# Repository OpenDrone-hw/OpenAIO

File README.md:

# OpenAIO

An all-in-one for 85 mm whoops, 2.5 inch cinewhoops and 3 inch freestyle: RP2354A flight controller, four AM32 ESC channels and an ExpressLRS 2.4 GHz
receiver on one 8-layer HDI board with 25.5 x 25.5 mm mounting. Its circuits follow OpenFC Lite 20x20, OpenESC-20x20 and
OpenRX-Lite.

## Why

Flight controller, ESC and receiver are usually three boards joined by connectors and wiring. On a small quad the
stack costs weight and height, and the connectors are where builds fail. OpenAIO puts all three on one board and keeps
the firmware stock. The market research linked under Prior art covers competing AIOs.

## Specifications

From the design files. Not manufactured yet.

| | |
|---|---|
| Mounting | 25.5 x 25.5 mm, four 3.0 mm holes |
| Board | 35.4 x 35.4 mm, 8 layers HDI 1+6+1, 0.997 mm, 1 oz copper on all layers, ENIG |
| Input | 3S to 6S LiPo, 9.0 to 25.2 V; 2S is not supported (gate driver VCC, see research/INPUT_RANGE.md) |
| Input protection | None: no reverse polarity protection, no TVS. Fit a low-ESR electrolytic of at least 35 V on the battery leads |
| Current rating | Not established; no measurement exists |
| Flight controller | RP2354A, BMI270 IMU, BMP580 barometer, USB-C |
| OSD and blackbox | Analog PIO framebuffer OSD, microSD card |
| ESC | 4x AM32, AT32F421G8U7 + NSG2065Q + 6x DOY180N03T (30 V) per channel, one shared current sensor |
| Receiver | ExpressLRS 2.4 GHz, ESP32-C3 + SX1281, u.FL antenna |
| Outputs | +10V (always on with a battery) on SH-6 and pads, +5V and +4v5 pads, WS2812 strip pads, buzzer pads |
| Firmware | Betaflight, AM32, ExpressLRS, stock upstream |

Technical write-up, part list and layout constraints: [AGENTS.md](AGENTS.md). Pinout and firmware:
[firmware/](firmware/README.md).

## Constraints

- 25.5 x 25.5 mm mounting, the whoop and toothpick standard.
- Runs stock firmware: Betaflight on the FC, AM32 per ESC channel, ExpressLRS on the receiver. No forks.
- Parts come from the shared library first; assembly from LCSC parts, extended parts kept to a minimum.
- 8-layer HDI 1+6+1 with filled microvias; fabrication limits are in [research/NEXTPCB.md](research/NEXTPCB.md).

## Prior art

- [OpenFC Lite 20x20](https://github.com/OpenDrone-hw/OpenFC-Lite-Mini): the RP2354A flight controller
- [OpenESC-20x20](https://github.com/OpenDrone-hw/OpenESC-20x20): the AM32 4-in-1 power stage
- [OpenRX Lite](https://github.com/OpenDrone-hw/OpenRX-Lite): the ELRS receiver
- [Market research](https://app.notion.com/p/3f5fe06764e1818e9158c512edd58138): competing toothpick and whoop AIOs, June 2026
- [Part alternatives](https://app.notion.com/p/3f5fe06764e1819eade0dc5bfbfdff7c): ESC-stage part alternatives, gate driver and FET options, March 2026
- [Current sensing](research/shunt/MARKET_AND_LITERATURE.md): shunt against copper sensing, market and literature

Notes: [input range](research/INPUT_RANGE.md), [pin constraints](research/IO-CONSTRAINTS.md),
[board data and copper model](research/ROUTING.md).

## Design questions

- Thermal: four power stages next to an MCU and a radio on 25.5 mm square, with no airflow guarantee. What is the
  continuous current budget on 1 oz copper? The copper loss model in [research/ROUTING.md](research/ROUTING.md) is the
  only number so far.
- RF isolation: a 2.4 GHz receiver next to four switching power stages: ground plane and antenna placement are
  untested.
- Open board issues: the LED strip stage inverts, the ESC MCUs run from USB without gate drive power, and SBUS on
  SH-6 shares a net with the ELRS TX: [firmware/ISSUES.md](firmware/ISSUES.md).

## In the line

What pairs with what, and what is available:
[opendrone.be](https://opendrone.be).

## Contributing

KiCad files cannot be merged, so say what you intend to change before you do,
on [Discord](https://discord.gg/v3sWmTcx3R). How everything works:
[CONTRIBUTING.md](CONTRIBUTING.md).

A repository holds design files only. Sourcing (suppliers, prices, quotes, RFQs, contacts) is handled by Incutec and never lives in OpenDrone repositories.

## License

Hardware licensed under [CERN-OHL-S-2.0](https://ohwr.org/cern_ohl_s_v2.txt),
see [LICENSE](LICENSE).

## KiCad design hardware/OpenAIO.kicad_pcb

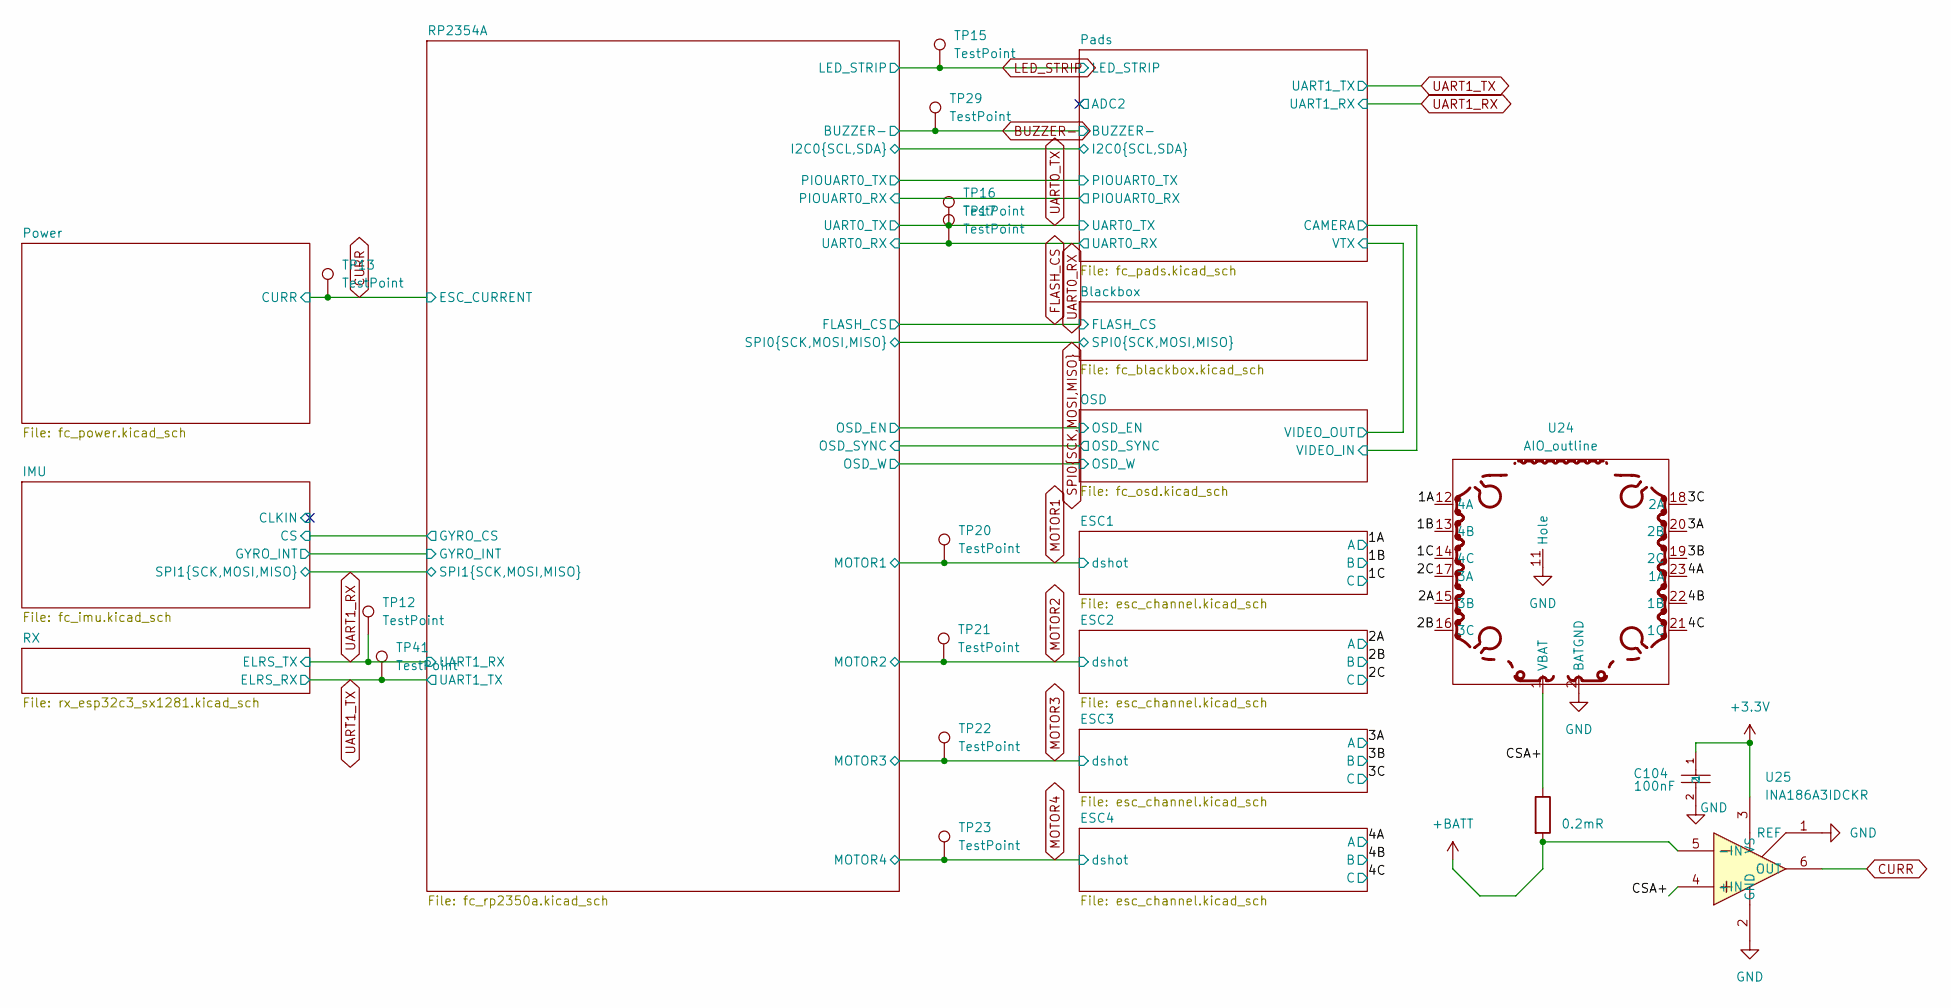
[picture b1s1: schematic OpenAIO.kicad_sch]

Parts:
C104: 100nF; C_0201_0603Metric; MPN GRM033R6YA104KE14D; LCSC C181043
Rsense2: 0.2mR; R_2512_6332Metric; MPN ASR-S-3-0.2F; LCSC C695806
TP12, TP13, TP15, TP16, TP17, TP20, TP21, TP22, TP23, TP29, TP41: TestPoint; TestPoint_Pad_D1.0mm
U24: AIO_outline
U25: INA186A3IDCKR; SOT-363_SC-70-6; MPN INA186A3IDCKR; LCSC C2058245

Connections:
+3.3V: C104.1, U25.3 (VS); also elsewhere on the board
+BATT: Rsense2.2, U25.5 (-IN); also elsewhere on the board
/1A: U24.12 (4A); also elsewhere on the board
/1B: U24.13 (4B); also elsewhere on the board
/1C: U24.14 (4C); also elsewhere on the board
/2A: U24.15 (3B); also elsewhere on the board
/2B: U24.16 (3C); also elsewhere on the board
/2C: U24.17 (3A); also elsewhere on the board
/3A: U24.20 (2B); also elsewhere on the board
/3B: U24.19 (2C); also elsewhere on the board
/3C: U24.18 (2A); also elsewhere on the board
/4A: U24.23 (1A); also elsewhere on the board
/4B: U24.22 (1B); also elsewhere on the board
/4C: U24.21 (1C); also elsewhere on the board
/CSA+: Rsense2.1, U24.1 (VBAT), U25.4 (+IN)
CURR: TP13.1, U25.6 (OUT); also elsewhere on the board
GND: C104.2, U24.2 (BATGND), U24.11 (Hole), U25.1 (REF), U25.2 (GND); also elsewhere on the board

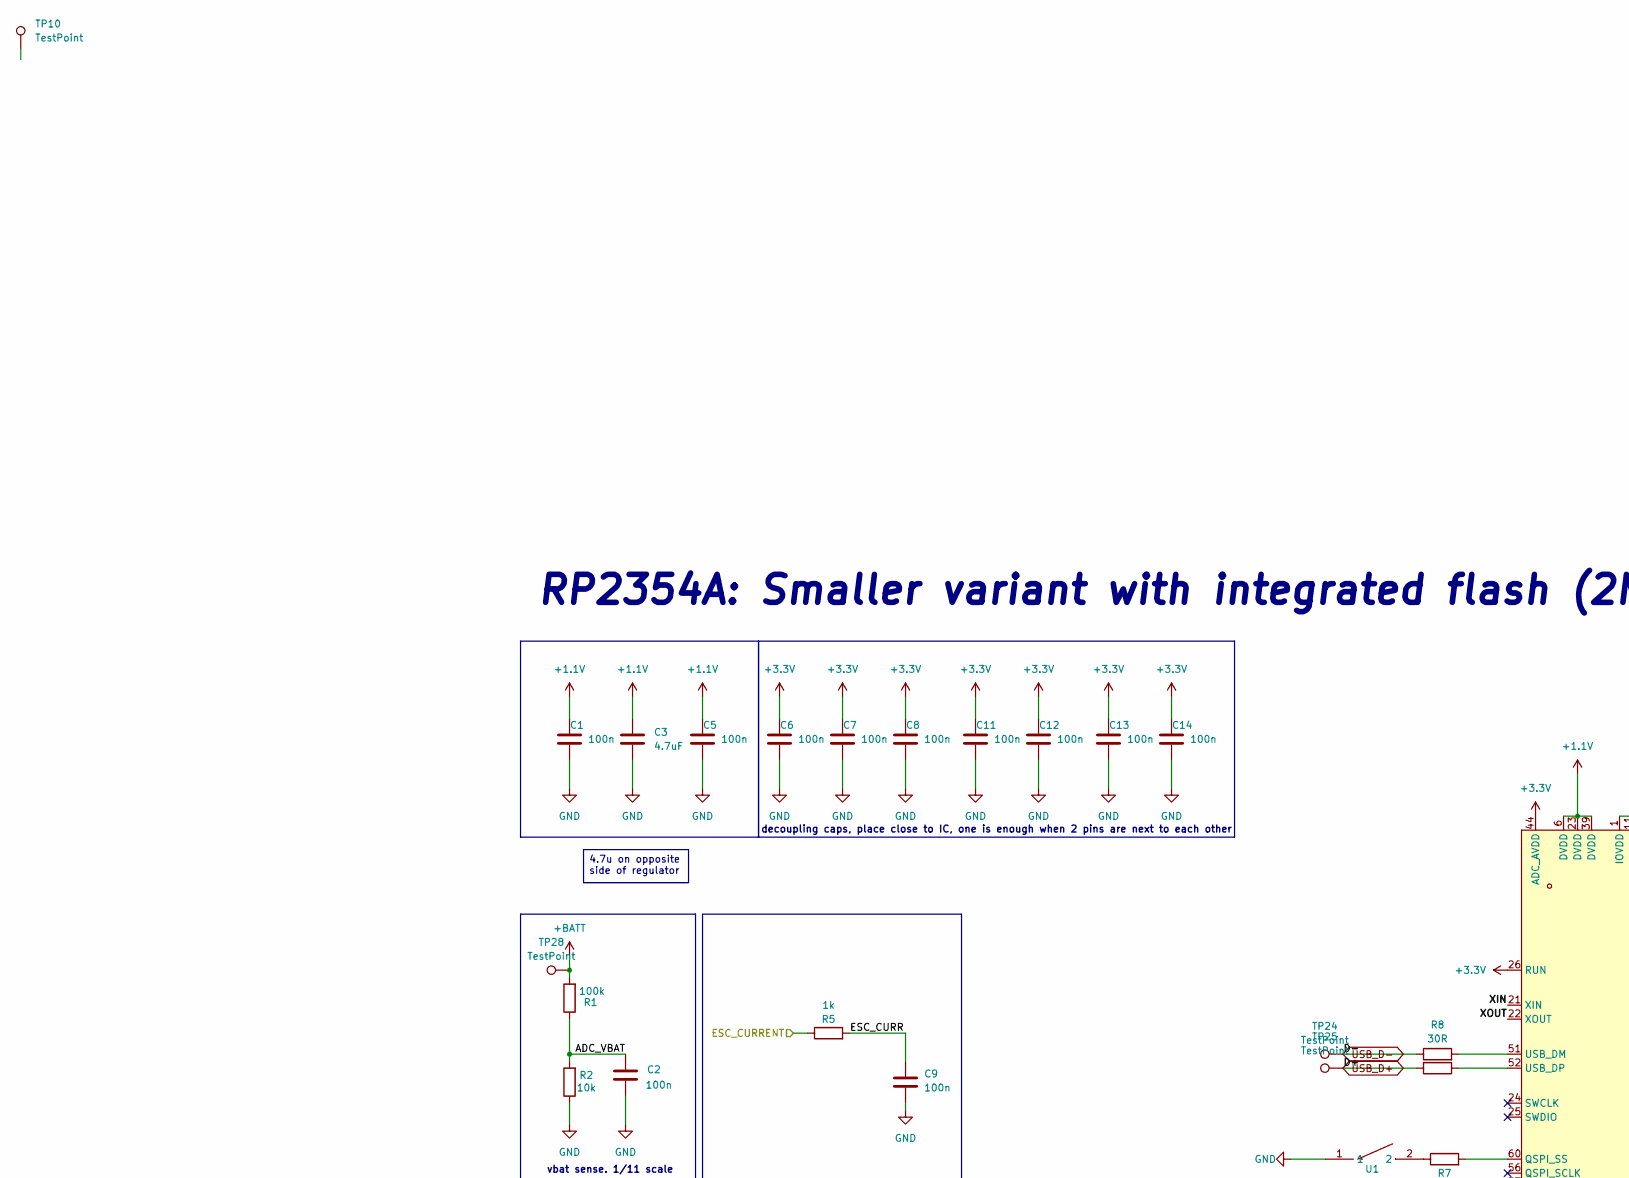
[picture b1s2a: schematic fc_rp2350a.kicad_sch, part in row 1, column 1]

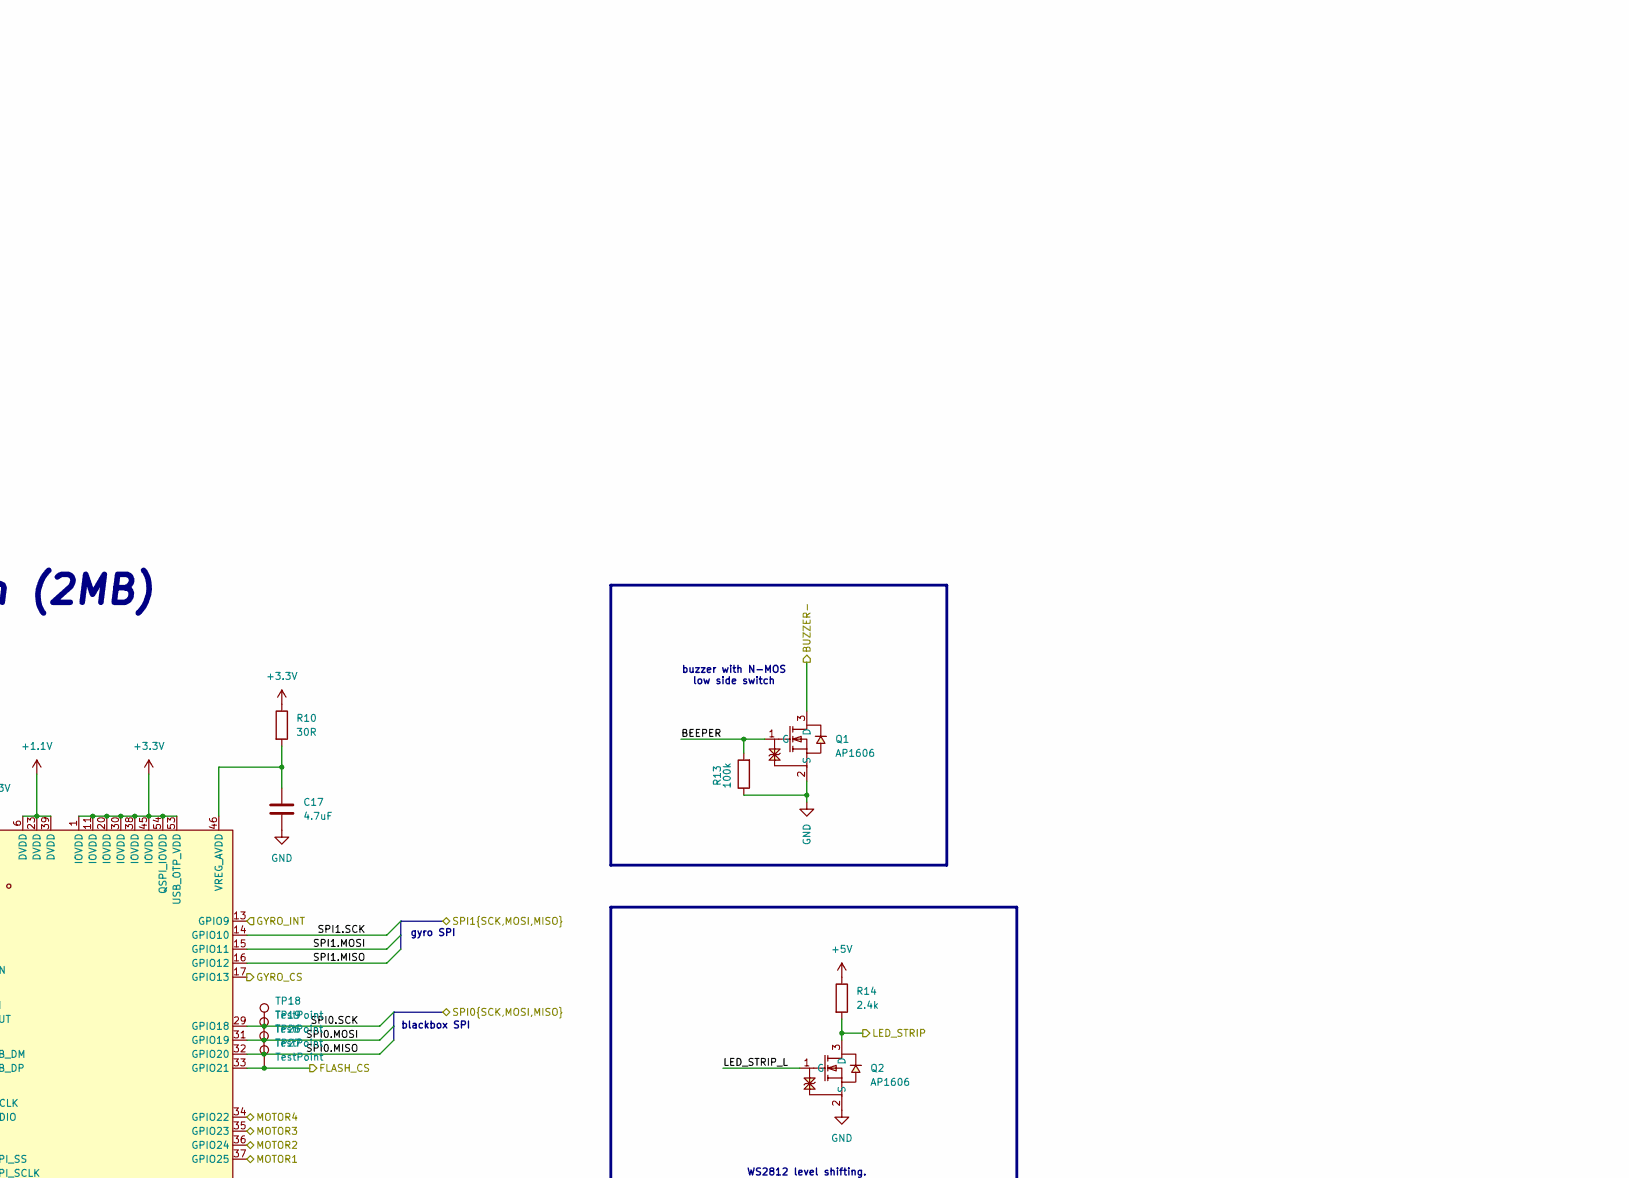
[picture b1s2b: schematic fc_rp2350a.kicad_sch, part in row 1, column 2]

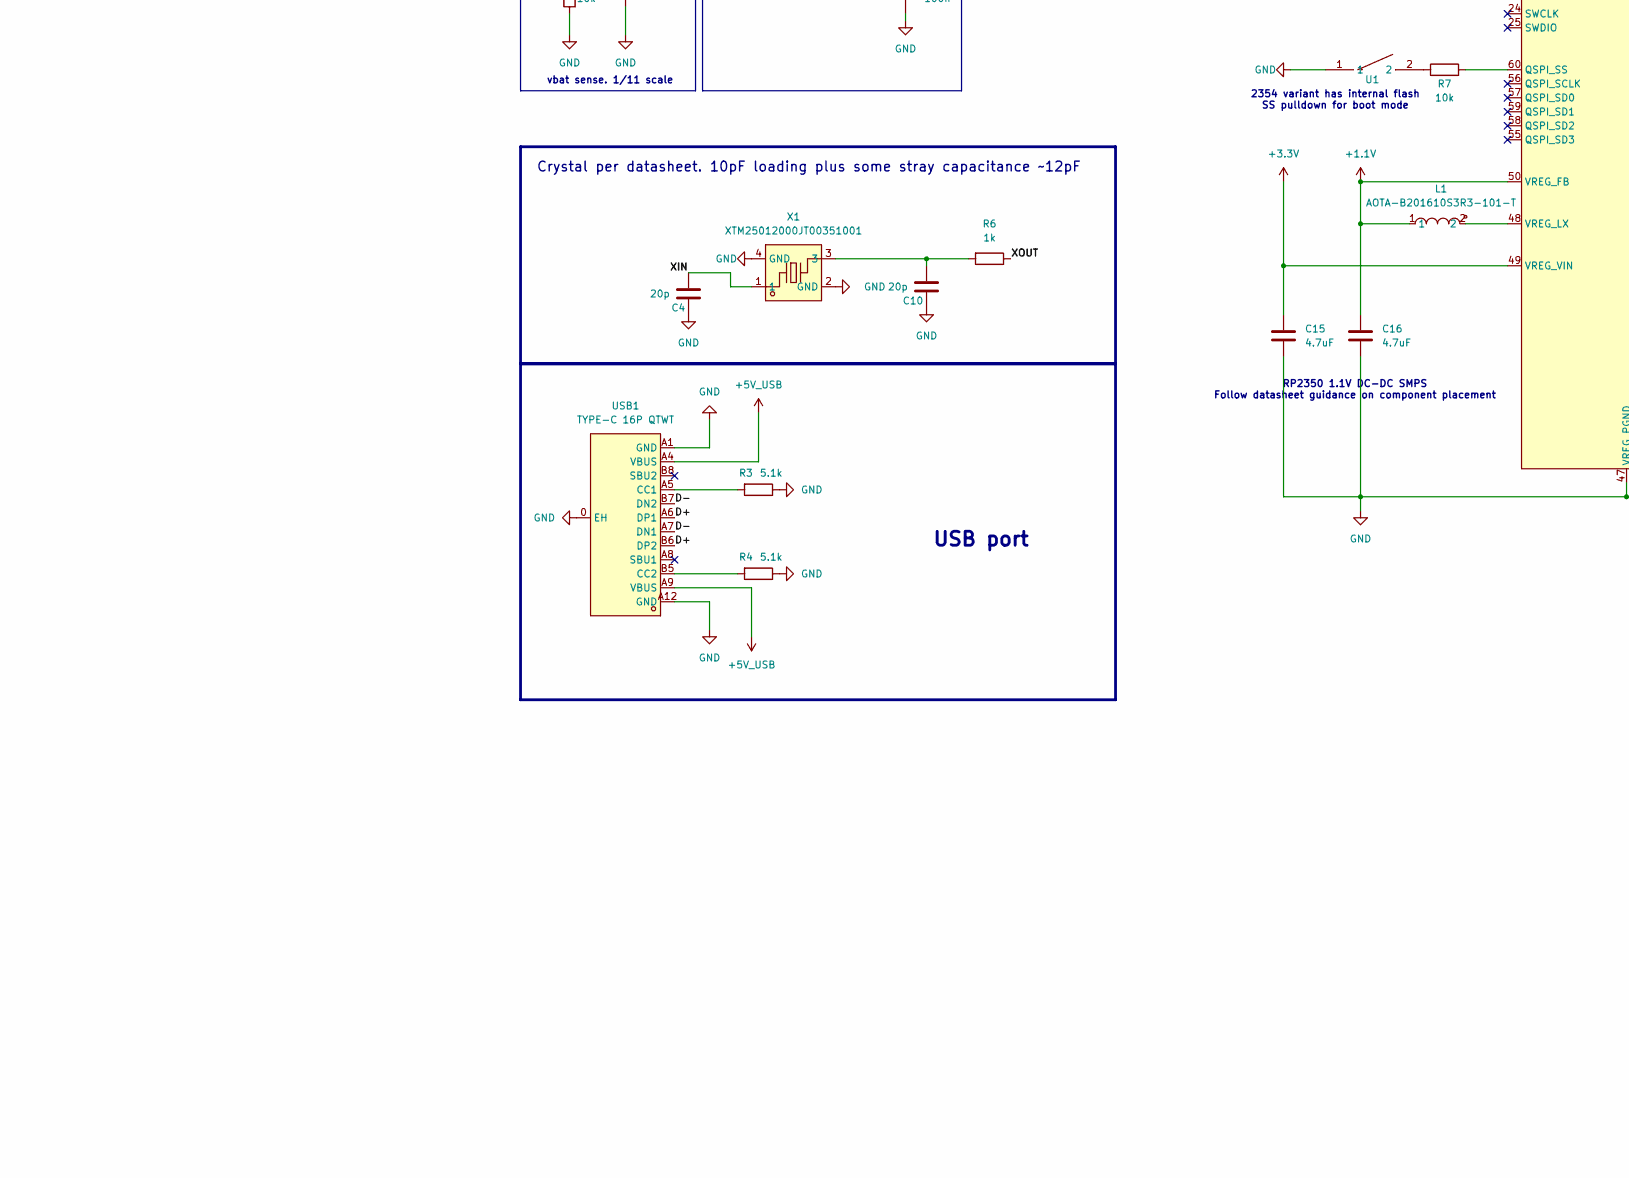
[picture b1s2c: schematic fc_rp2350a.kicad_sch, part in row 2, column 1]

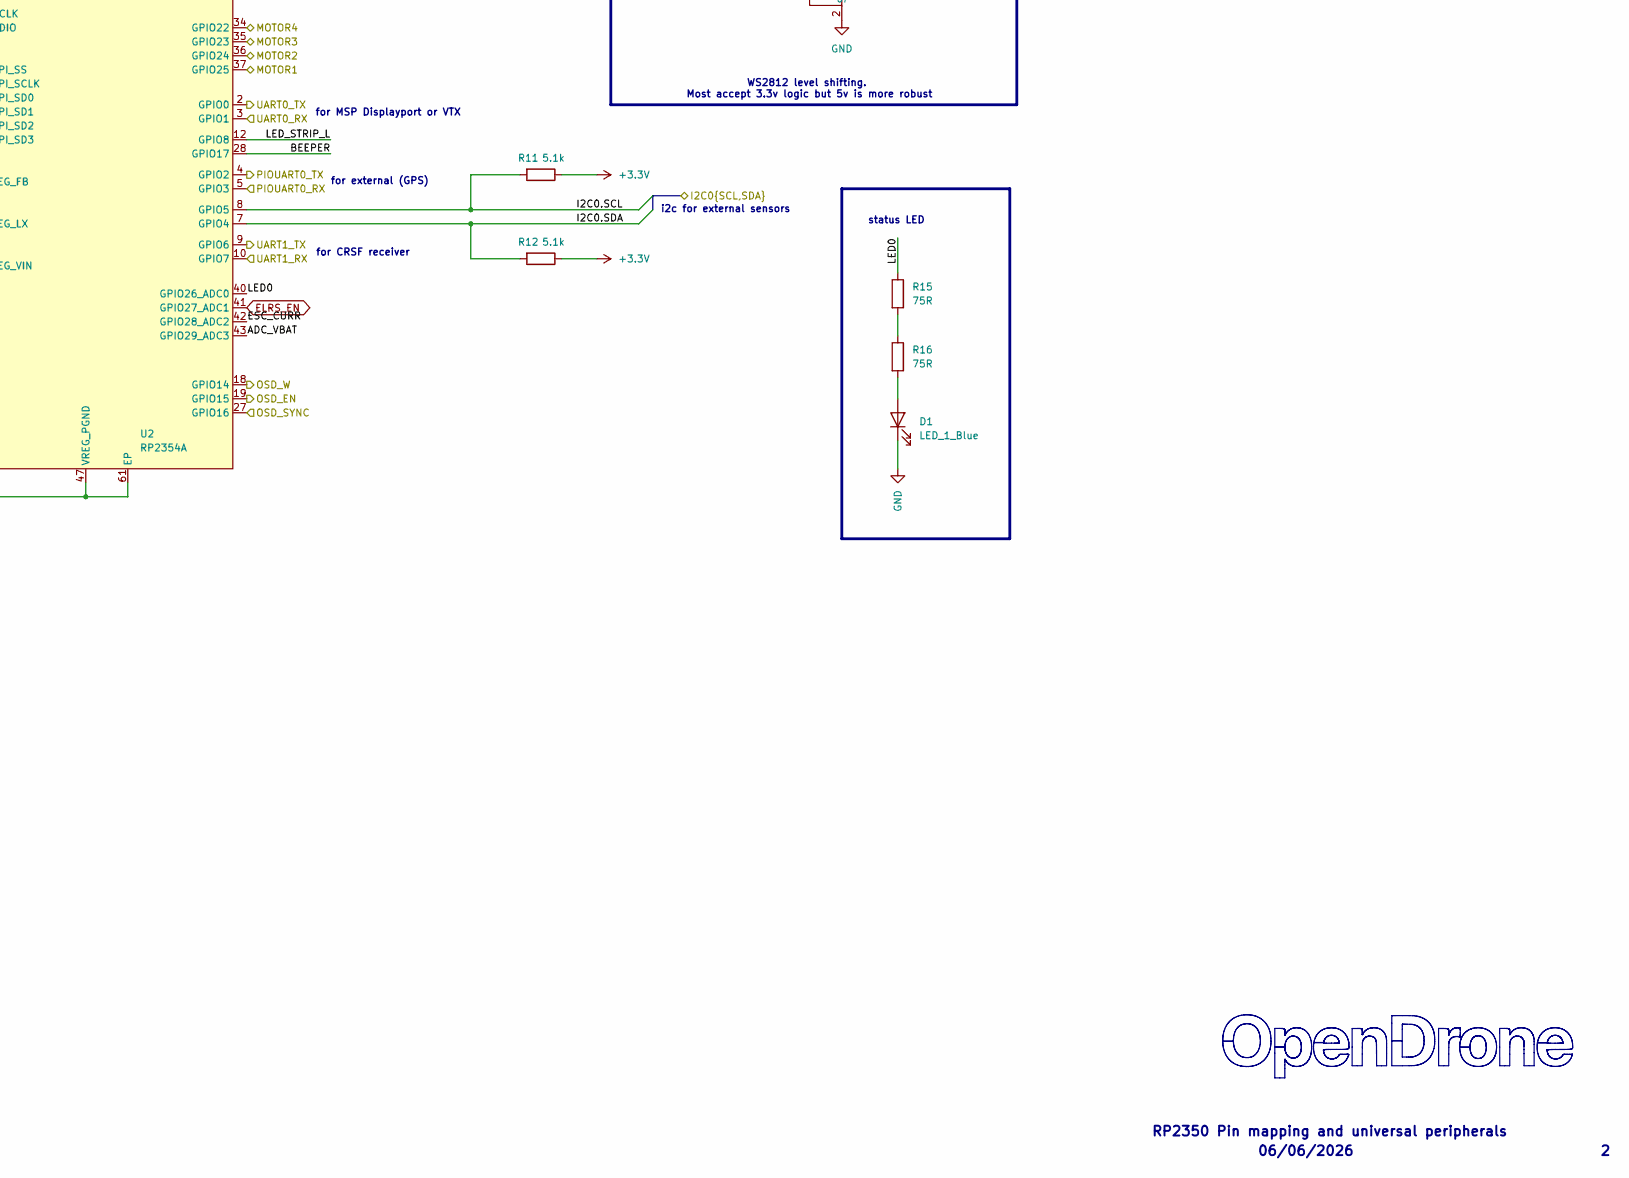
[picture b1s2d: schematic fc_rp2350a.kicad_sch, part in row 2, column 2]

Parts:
C1, C2, C5, C6, C7, C8, C9, C11, C12, C13, C14: 100n; C_0201_0603Metric; MPN GRM033R61E104KE14D; LCSC C76939
C3, C15, C16, C17: 4.7uF; C_0402_1005Metric; MPN CL05A475MP5NRNC; LCSC C23733
C4, C10: 20p; C_0201_0603Metric; MPN GRM0335C1H200JA01D; LCSC C76923
D1: LED_1_Blue; LED_0402_1005Metric; MPN XL-1005UBC; LCSC C22355736
L1: AOTA-B201610S3R3-101-T; IND-SMD_L2.0-W1.6_AOTA-B201610S3R3-101-T; MPN AOTA-B201610S3R3-101-T; LCSC C42411119
Q1, Q2: AP1606; DFN-3L_L1.0-W0.6-P0.65-BR; MPN AP1606; LCSC C2849580
R1, R13: 100k; R_0201_0603Metric; MPN 0201WMF1003TEE; LCSC C270364
R2, R7: 10k; R_0201_0603Metric; MPN RC0201FR-0710KL; LCSC C106225
R3, R4, R11, R12: 5.1k; R_0201_0603Metric; MPN 0201WMF5101TEE; LCSC C270344
R5, R6: 1k; R_0201_0603Metric; MPN 0201WMF1001TEE; LCSC C270365
R8, R9, R10: 30R; R_0201_0603Metric; MPN NQ01WMJ0300TEE; LCSC C778391
R14: 2.4k; R_0201_0603Metric; LCSC C166281
R15, R16: 75R; R_0201_0603Metric; MPN RC0201FR-0775RL; LCSC C274878
TP10, TP18, TP19, TP24, TP25, TP26, TP27, TP28: TestPoint; TestPoint_Pad_D1.0mm
U1: TS2306A 240GF MSM 9_C2976675; SW-SMD_4P-L3.0-W2.0-P0.85-LS3.5; MPN TS2306A 240gf MSM 9; LCSC C2976675
U2: RP2354A; QFN-60_L7.0-W7.0-P0.40-TL-EP3.4; MPN RP2354A; LCSC C41378174
USB1: TYPE-C 16P QTWT; USB-TYPE-C-SMD_TYPE-C-16P-QTWT; MPN TYPE-C 16P QTWT; LCSC C5187472
X1: XTM25012000JT00351001; CRYSTAL-SMD_4P-L2.5-W2.0-BL-A; MPN XTM25012000JT00351001; LCSC C37635340

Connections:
+1.1V: C1.1, C3.1, C5.1, C16.1, L1.1, U2.6 (DVDD), U2.23 (DVDD), U2.39 (DVDD), U2.50 (VREG_FB)
+3.3V: C6.1, C7.1, C8.1, C11.1, C12.1, C13.1, C14.1, C15.1, R10.1, R11.1, R12.1, U2.1 (IOVDD), U2.11 (IOVDD), U2.20 (IOVDD), U2.26 (RUN), U2.30 (IOVDD), U2.38 (IOVDD), U2.44 (ADC_AVDD), U2.45 (IOVDD), U2.49 (VREG_VIN), U2.53 (USB_OTP_VDD), U2.54 (QSPI_IOVDD); also elsewhere on the board
+5V: R14.1; also elsewhere on the board
+5V_USB: USB1.A4 (VBUS), USB1.A9 (VBUS); also elsewhere on the board
+BATT: R1.2, TP28.1; also elsewhere on the board
/IMU/CS: U2.17 (GPIO13); also elsewhere on the board
/IMU/GYRO_INT: U2.13 (GPIO9); also elsewhere on the board
/IMU/SPI1.MISO: U2.16 (GPIO12); also elsewhere on the board
/IMU/SPI1.MOSI: U2.15 (GPIO11); also elsewhere on the board
/IMU/SPI1.SCK: U2.14 (GPIO10); also elsewhere on the board
/OSD/OSD_EN: U2.19 (GPIO15); also elsewhere on the board
/OSD/OSD_SYNC: U2.27 (GPIO16); also elsewhere on the board
/OSD/OSD_W: U2.18 (GPIO14); also elsewhere on the board
/Pads/I2C0.SCL: R11.2, U2.8 (GPIO5); also elsewhere on the board
/Pads/I2C0.SDA: R12.2, U2.7 (GPIO4); also elsewhere on the board
/Pads/PIOUART0_TX: U2.4 (GPIO2); also elsewhere on the board
/Pads/PU0RX: U2.5 (GPIO3); also elsewhere on the board
/RP2354A/ADC_VBAT: C2.2, R1.1, R2.2, U2.43 (GPIO29_ADC3)
/RP2354A/BEEPER: Q1.1 (G), R13.2, U2.28 (GPIO17)
/RP2354A/ESC_CURR: C9.1, R5.2, U2.42 (GPIO28_ADC2)
/RP2354A/LED0: R15.1, U2.40 (GPIO26_ADC0)
/RP2354A/LED_STRIP_L: Q2.1 (G), U2.12 (GPIO8)
/RP2354A/XIN: C4.2, U2.21 (XIN), X1.1
/RP2354A/XOUT: R6.1, U2.22 (XOUT)
BUZZER-: Q1.3 (D); also elsewhere on the board
CURR: R5.1; also elsewhere on the board
ELRS_EN: U2.41 (GPIO27_ADC1); also elsewhere on the board
FLASH_CS: TP27.1, U2.33 (GPIO21); also elsewhere on the board
GND: C1.2, C2.1, C3.2, C4.1, C5.2, C6.2, C7.2, C8.2, C9.2, C10.1, C11.2, C12.2, C13.2, C14.2, C15.2, C16.2, C17.2, D1.1 (K), Q1.2 (S), Q2.2 (S), R2.1, R3.1, R4.1, R13.1, U1.1, U2.47 (VREG_PGND), U2.61 (EP), USB1.0 (EH), USB1.A1 (GND), USB1.A12 (GND), X1.2 (GND), X1.4 (GND); also elsewhere on the board
LED_STRIP: Q2.3 (D), R14.2; also elsewhere on the board
MOTOR1: U2.37 (GPIO25); also elsewhere on the board
MOTOR2: U2.36 (GPIO24); also elsewhere on the board
MOTOR3: U2.35 (GPIO23); also elsewhere on the board
MOTOR4: U2.34 (GPIO22); also elsewhere on the board
unnamed: C10.2, R6.2, X1.3
unnamed: D1.2 (A), R16.2
unnamed: R7.1, U1.2
unnamed: R15.2, R16.1
unnamed: R7.2, U2.60 (QSPI_SS)
unnamed: R8.2, U2.51 (USB_DM)
unnamed: R9.1, U2.52 (USB_DP)
unnamed: C17.1, R10.2, U2.46 (VREG_AVDD)
unnamed: L1.2, U2.48 (VREG_LX)
unnamed: R3.2, USB1.A5 (CC1)
unnamed: R4.2, USB1.B5 (CC2)
SPI0.MISO: TP26.1, U2.32 (GPIO20); also elsewhere on the board
SPI0.MOSI: TP19.1, U2.31 (GPIO19); also elsewhere on the board
SPI0.SCK: TP18.1, U2.29 (GPIO18); also elsewhere on the board
UART0_RX: U2.3 (GPIO1); also elsewhere on the board
UART0_TX: U2.2 (GPIO0); also elsewhere on the board
UART1_RX: U2.10 (GPIO7); also elsewhere on the board
UART1_TX: U2.9 (GPIO6); also elsewhere on the board
USB_D+: R9.2, TP25.1, USB1.A6 (DP1), USB1.B6 (DP2)
USB_D-: R8.1, TP24.1, USB1.A7 (DN1), USB1.B7 (DN2)

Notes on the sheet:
blackbox SPI
vbat sense. 1/11 scale
RP2354A: Smaller variant with integrated flash (2MB)
06/06/2026
buzzer with N-MOS low side switch
RP2350 Pin mapping and universal peripherals
2354 variant has internal flash SS pulldown for boot mode
decoupling caps, place close to IC, one is enough when 2 pins are next to each other
RP2350 1.1V DC-DC SMPS Follow datasheet guidance on component placement
status LED
for external (GPS)
i2c for external sensors
gyro SPI
for CRSF receiver
WS2812 level shifting. Most accept 3.3v logic but 5v is more robust
for MSP Displayport or VTX
Crystal per datasheet. 10pF loading plus some stray capacitance ~12pF
USB port
4.7u on opposite side of regulator

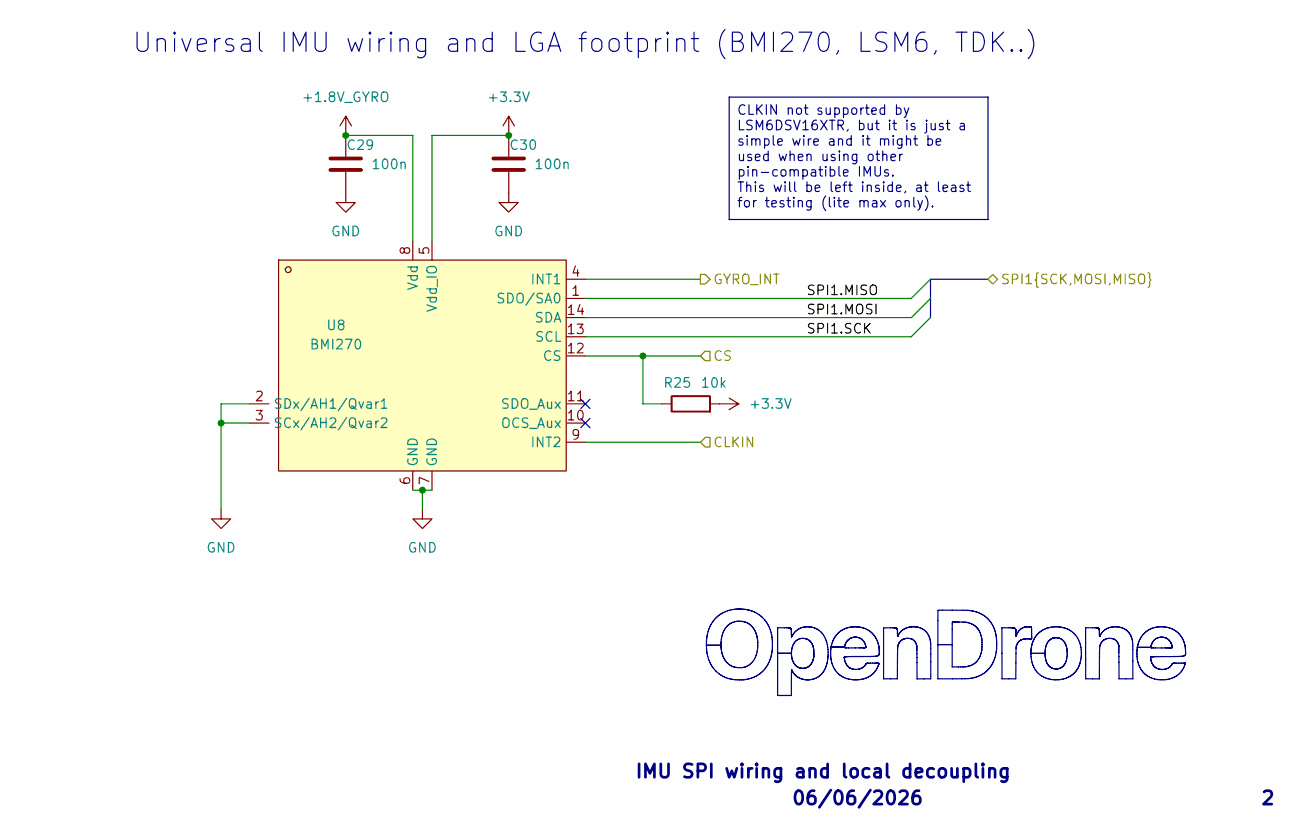
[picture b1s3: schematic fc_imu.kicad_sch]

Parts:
C29, C30: 100n; C_0201_0603Metric; MPN GRM033R61E104KE14D; LCSC C76939
R25: 10k; R_0201_0603Metric; MPN RC0201FR-0710KL; LCSC C106225
U8: BMI270; LGA-14_L3.0-W2.5-P0.50-BR; MPN BMI270; LCSC C2836813

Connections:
+1.8V_GYRO: C29.1, U8.8 (Vdd); also elsewhere on the board
+3.3V: C30.1, R25.2, U8.5 (Vdd_IO); also elsewhere on the board
/IMU/CLKIN: U8.9 (INT2)
/IMU/CS: R25.1, U8.12 (CS); also elsewhere on the board
/IMU/GYRO_INT: U8.4 (INT1); also elsewhere on the board
/IMU/SPI1.MISO: U8.1 (SDO/SA0); also elsewhere on the board
/IMU/SPI1.MOSI: U8.14 (SDA); also elsewhere on the board
/IMU/SPI1.SCK: U8.13 (SCL); also elsewhere on the board
GND: C29.2, C30.2, U8.2 (SDx/AH1/Qvar1), U8.3 (SCx/AH2/Qvar2), U8.6 (GND), U8.7 (GND); also elsewhere on the board

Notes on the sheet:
06/06/2026
Universal IMU wiring and LGA footprint (BMI270, LSM6, TDK..)
IMU SPI wiring and local decoupling
CLKIN not supported by LSM6DSV16XTR, but it is just a simple wire and it might be used when using other pin-compatible IMUs. This will be left inside, at least for testing (lite max only).

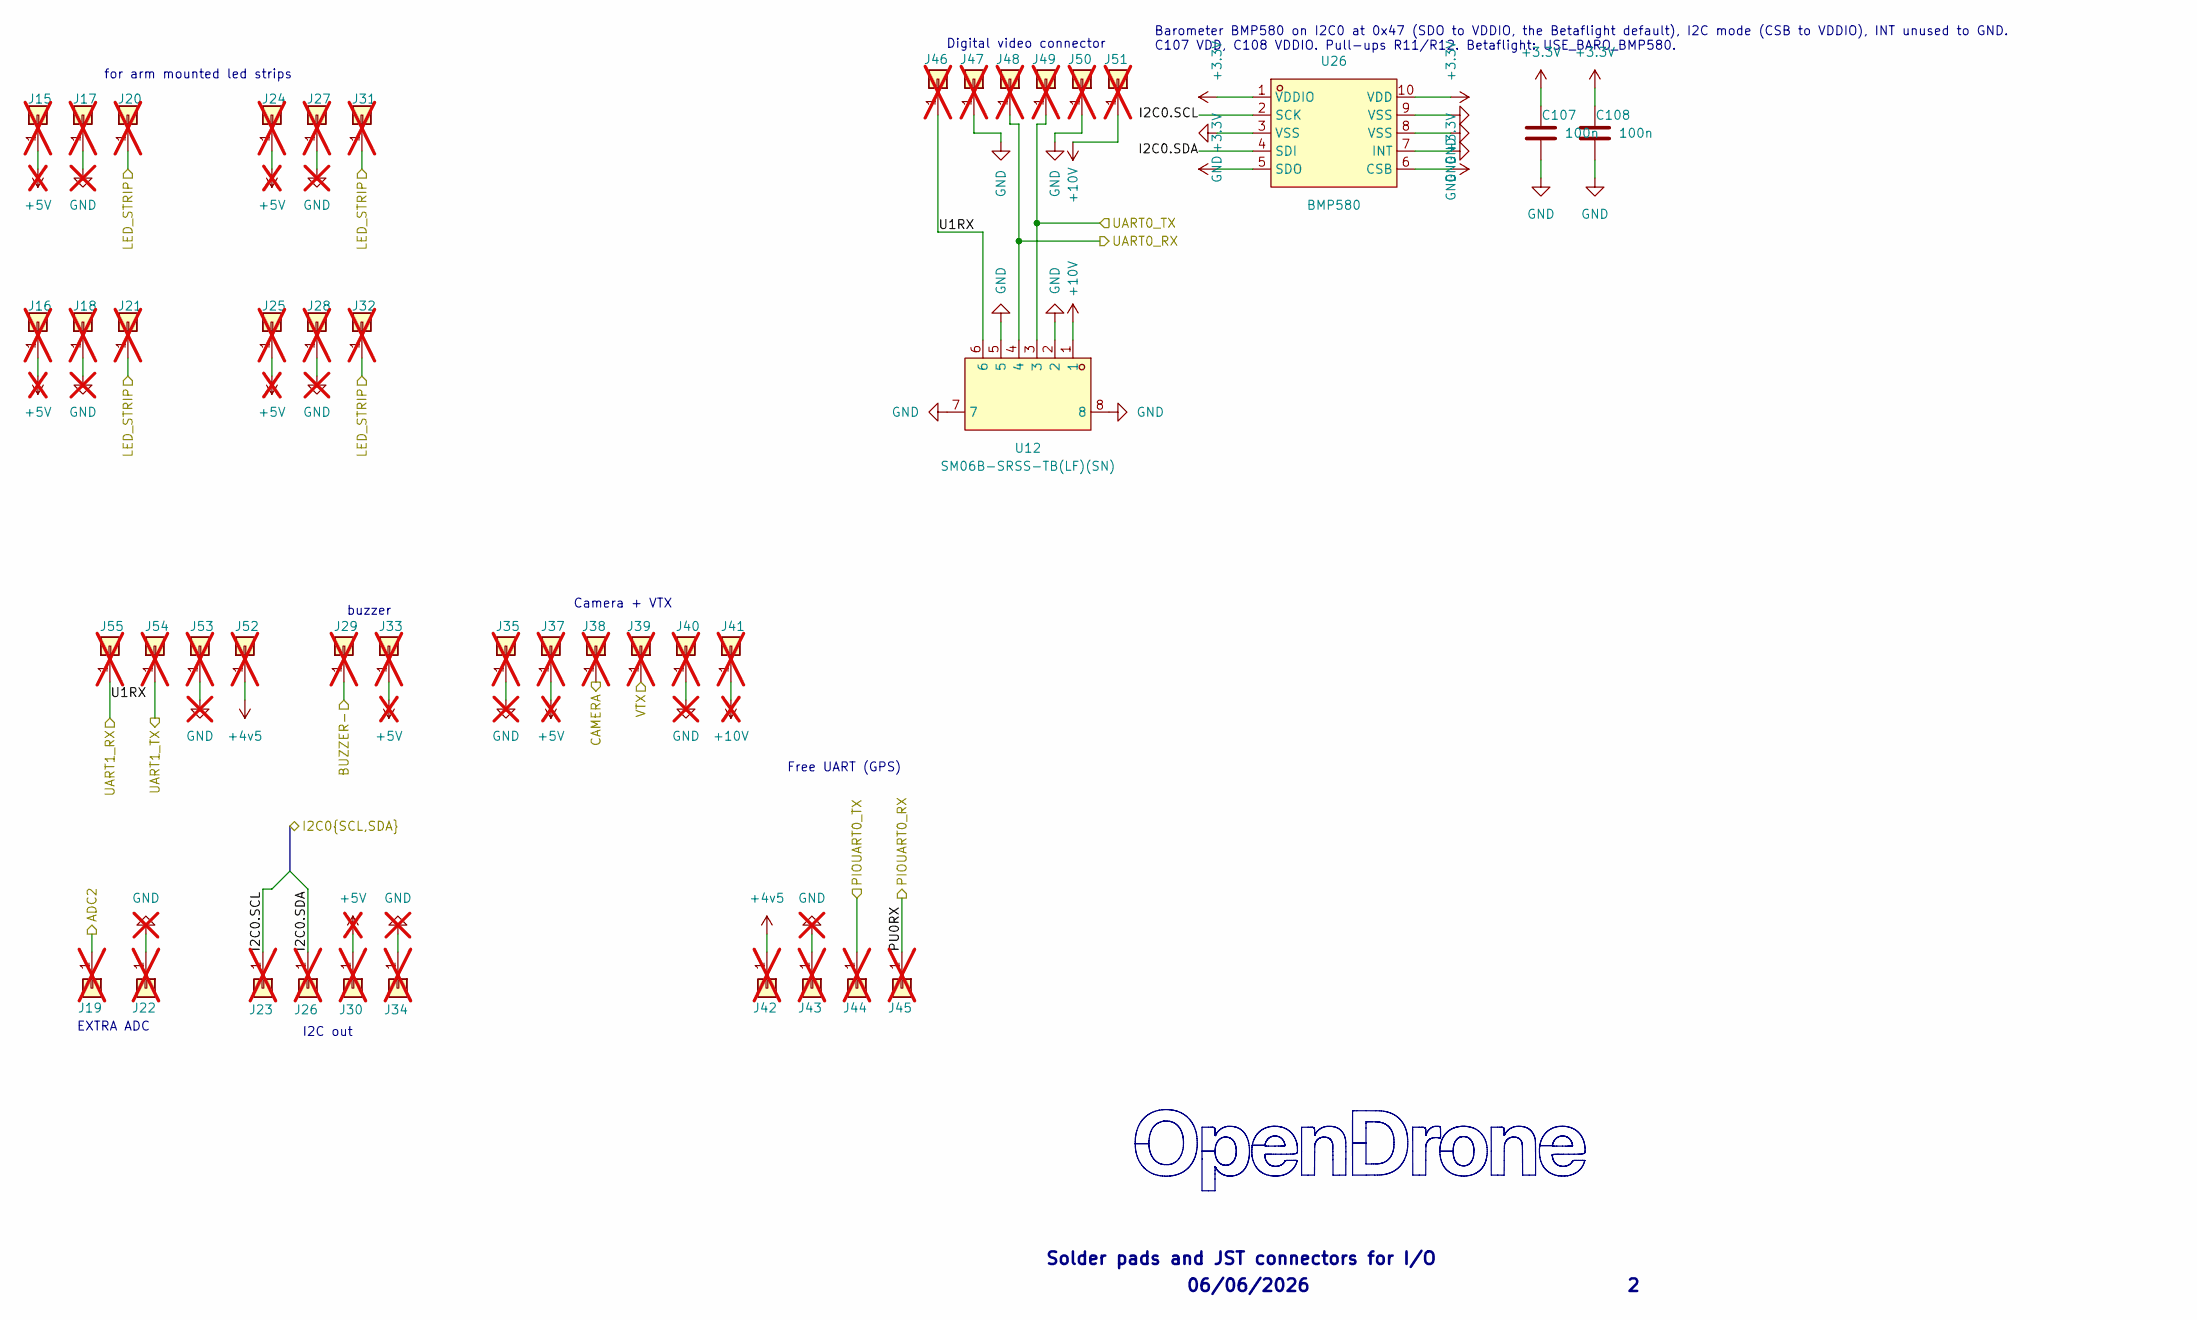
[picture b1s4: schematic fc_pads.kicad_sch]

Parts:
C107, C108: 100n; C_0201_0603Metric; MPN GRM033R61E104KE14D; LCSC C76939
J15, J16, J17, J18, J19, J20, J21, J22, J23, J24, J25, J26, J27, J28, J29, J30, J31, J32, J33, J34, J35, J37, J38, J39, J40, J41, J42, J43, J44, J45, J46, J47, J48, J49, J50, J51, J52, J53, J54, J55: 5V; small_pad; not fitted
U12: SM06B-SRSS-TB(LF)(SN); CONN-SMD_SM06B-SRSS-TB-LF-SN; MPN SM06B-SRSS-TB(LF)(SN); LCSC C160405
U26: BMP580; LGA-10_L2.0-W2.0-P0.50-TL_BMP580; MPN BMP580; LCSC C22391138

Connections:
+3.3V: C107.1, C108.1, U26.1 (VDDIO), U26.5 (SDO), U26.6 (CSB), U26.10 (VDD); also elsewhere on the board
+4v5: J42.1 (Pin_1_1), J52.1 (Pin_1_1); also elsewhere on the board
+5V: J15.1 (Pin_1_1), J16.1 (Pin_1_1), J24.1 (Pin_1_1), J25.1 (Pin_1_1), J30.1 (Pin_1_1), J33.1 (Pin_1_1), J37.1 (Pin_1_1); also elsewhere on the board
+10V: J41.1 (Pin_1_1), J51.1 (Pin_1_1), U12.1; also elsewhere on the board
/OSD/VIDEO_IN: J38.1 (Pin_1_1); also elsewhere on the board
/OSD/VIDEO_OUT: J39.1 (Pin_1_1); also elsewhere on the board
/Pads/I2C0.SCL: J23.1 (Pin_1_1), U26.2 (SCK); also elsewhere on the board
/Pads/I2C0.SDA: J26.1 (Pin_1_1), U26.4 (SDI); also elsewhere on the board
/Pads/PIOUART0_TX: J44.1 (Pin_1_1); also elsewhere on the board
/Pads/PU0RX: J45.1 (Pin_1_1); also elsewhere on the board
BUZZER-: J29.1 (Pin_1_1); also elsewhere on the board
GND: C107.2, C108.2, J17.1 (Pin_1_1), J18.1 (Pin_1_1), J22.1, J27.1 (Pin_1_1), J28.1 (Pin_1_1), J34.1 (Pin_1_1), J35.1 (Pin_1_1), J40.1 (Pin_1_1), J43.1 (Pin_1_1), J47.1, J50.1 (Pin_1_1), J53.1 (Pin_1_1), U12.2, U12.5, U12.7, U12.8, U26.3 (VSS), U26.7 (INT), U26.8 (VSS), U26.9 (VSS); also elsewhere on the board
LED_STRIP: J20.1 (Pin_1_1), J21.1 (Pin_1_1), J31.1 (Pin_1_1), J32.1 (Pin_1_1); also elsewhere on the board
UART0_RX: J48.1 (Pin_1_1), U12.4; also elsewhere on the board
UART0_TX: J49.1 (Pin_1_1), U12.3; also elsewhere on the board
UART1_RX: J46.1, J55.1 (Pin_1_1), U12.6; also elsewhere on the board
UART1_TX: J54.1 (Pin_1_1); also elsewhere on the board

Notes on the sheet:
Free UART (GPS)
I2C out
Solder pads and JST connectors for I/O
06/06/2026
buzzer
Camera + VTX
Barometer BMP580 on I2C0 at 0x47 (SDO to VDDIO, the Betaflight default), I2C mode (CSB to VDDIO), INT unused to GND. C107 VDD, C108 VDDIO. Pull-ups R11/R12. Betaflight: USE_BARO_BMP580.
Digital video connector
EXTRA ADC
for arm mounted led strips

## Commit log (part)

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2026-04-11 Reorganize project tree, consolidate into single local library
    - Re-fetch all 9 schematics verbatim from source repos (OpenFC-ECO,
    4in1ESC 2, OpenRX-Lite) into schematics/{fc,esc,elrs}/
    - Merge symbols/footprints/3D models into libs/lib.{kicad_sym,pretty,3dshapes}
    - Extract only symbols/footprints actually referenced by schematics (43
    symbols, 44 footprints, 38 3D models) — no dead bloat
    - Rewrite schematic lib_ids to single `lib:` nickname via kicad-skip
2026-04-11 Root sheet, initial ESC1 layout, multichannel rule areas
    - Create OpenAIO.kicad_sch root sheet with hierarchical sheet symbols
    pointing to schematics/{fc,esc,elrs}/ sub-sheets
    - Rewrite root-sheet lib_ids to single `lib:` nickname (caught stale
    ESCLibrary:/components:/4in1ESC: refs that were baked in before lib
    consolidation)
    - Place 12x MotorPad and 2x BatteryPad symbols on root sheet
